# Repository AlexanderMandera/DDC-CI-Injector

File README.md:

# DDC/CI Injector using PCA9641

(work in progress, not working!)

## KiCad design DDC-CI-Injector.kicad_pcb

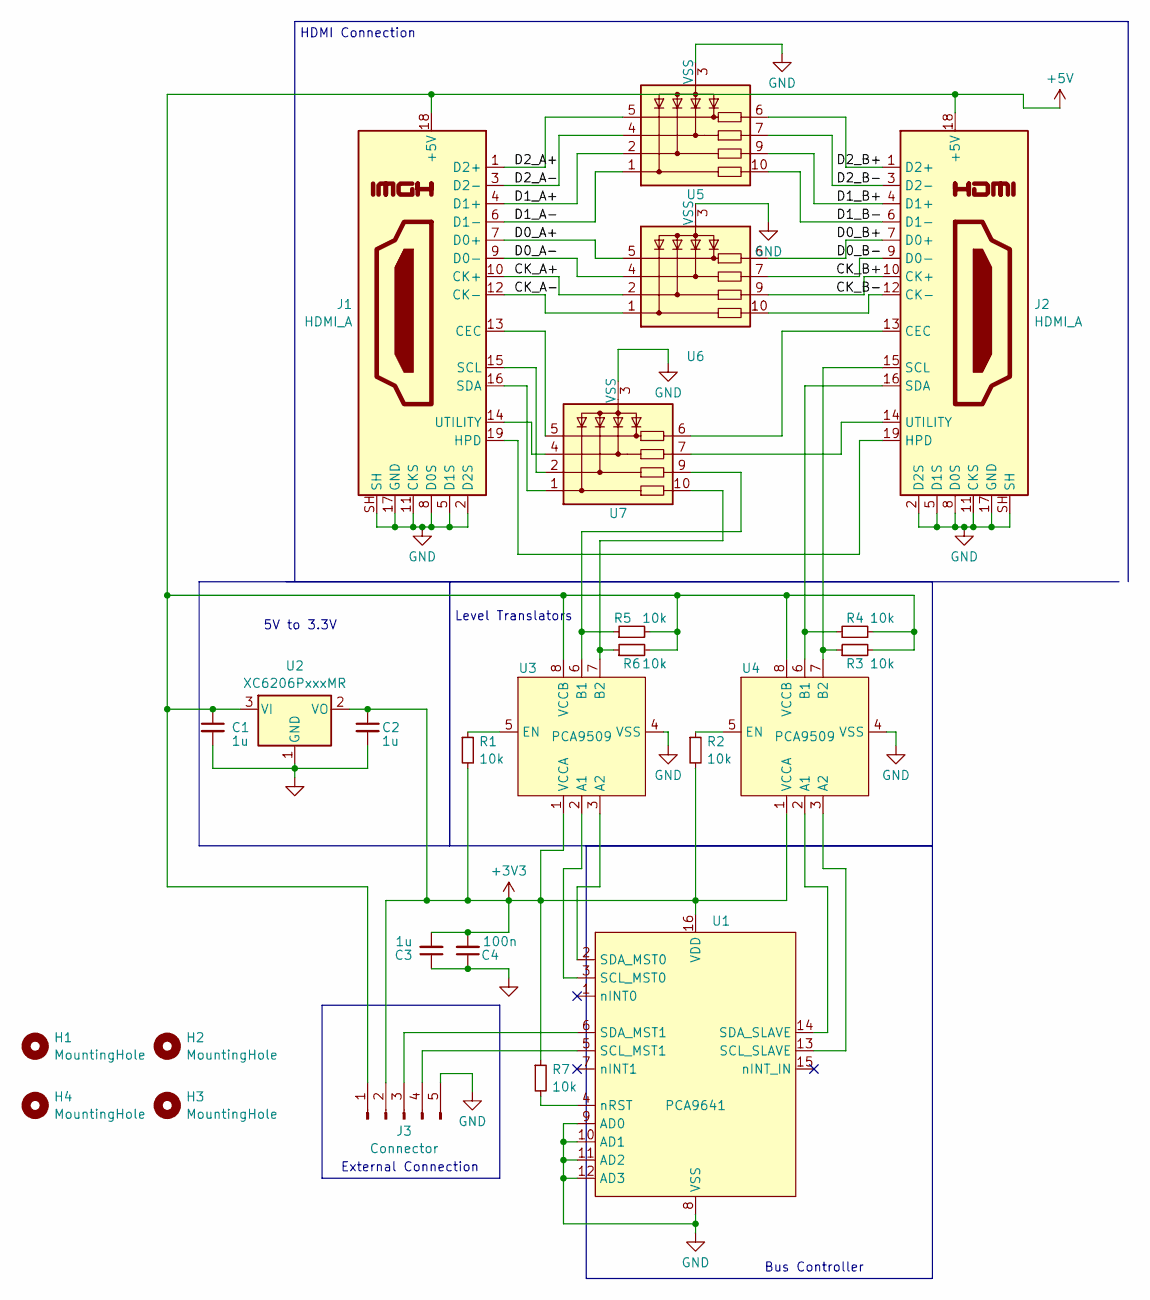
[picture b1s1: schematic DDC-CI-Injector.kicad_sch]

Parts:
C1, C2, C3: 1u; C_0603_1608Metric
C4: 100n; C_0402_1005Metric
H1, H2, H3, H4: MountingHole; MountingHole_2.7mm_M2.5_DIN965
J1, J2: HDMI_A; HDMI_A_Molex_208658-1001_Horizontal
J3: Connector; PinHeader_1x05_P2.54mm_Vertical
R1, R2, R3, R4, R5, R6, R7: 10k; R_0402_1005Metric
U1: PCA9641; TSSOP-16_4.4x5mm_P0.65mm
U2: XC6206PxxxMR; SOT-23-3
U3, U4: PCA9509; TSSOP-8_3x3mm_P0.65mm
U5, U6, U7: ESD224DQA; Diodes_UDFN-10_1.0x2.5mm_P0.5mm

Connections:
+3V3: C2.1, C3.2, C4.2, J3.2, R1.2, R2.2, R7.1, U1.16 (VDD), U2.2 (VO), U3.1 (VCCA), U4.1 (VCCA)
+5V: C1.1, J1.18 (+5V), J2.18 (+5V), J3.1, R3.2, R4.2, R5.2, R6.2, U2.3 (VI), U3.8 (VCCB), U4.8 (VCCB)
/CK_A+: J1.10 (CK+), U6.2
/CK_A-: J1.12 (CK-), U6.1
/CK_B+: J2.10 (CK+), U6.9
/CK_B-: J2.12 (CK-), U6.10
/D0_A+: J1.7 (D0+), U6.5
/D0_A-: J1.9 (D0-), U6.4
/D0_B+: J2.7 (D0+), U6.6
/D0_B-: J2.9 (D0-), U6.7
/D1_A+: J1.4 (D1+), U5.2
/D1_A-: J1.6 (D1-), U5.1
/D1_B+: J2.4 (D1+), U5.9
/D1_B-: J2.6 (D1-), U5.10
/D2_A+: J1.1 (D2+), U5.5
/D2_A-: J1.3 (D2-), U5.4
/D2_B+: J2.1 (D2+), U5.6
/D2_B-: J2.3 (D2-), U5.7
GND: C1.2, C2.2, C3.1, C4.1, J1.2 (D2S), J1.5 (D1S), J1.8 (D0S), J1.11 (CKS), J1.17 (GND), J1.SH, J2.2 (D2S), J2.5 (D1S), J2.8 (D0S), J2.11 (CKS), J2.17 (GND), J2.SH, J3.5, U1.8 (VSS), U1.9 (AD0), U1.10 (AD1), U1.11 (AD2), U1.12 (AD3), U2.1 (GND), U3.4 (VSS), U4.4 (VSS), U5.3 (VSS), U5.8 (VSS), U6.3 (VSS), U6.8 (VSS), U7.3 (VSS), U7.8 (VSS)
unnamed: J1.13 (CEC), U7.5
unnamed: J1.19 (HPD), J2.19 (HPD)
unnamed: J1.15 (SCL), U7.2
unnamed: J1.16 (SDA), U7.1
unnamed: J1.14 (UTILITY), U7.4
unnamed: J2.13 (CEC), U7.6
unnamed: J2.15 (SCL), R3.1, U4.7 (B2)
unnamed: J2.16 (SDA), R4.1, U4.6 (B1)
unnamed: J2.14 (UTILITY), U7.7
unnamed: J3.3, U1.6 (SDA_MST1)
unnamed: J3.4, U1.5 (SCL_MST1)
unnamed: U1.3 (SCL_MST0), U3.2 (A1)
unnamed: U1.13 (SCL_SLAVE), U4.3 (A2)
unnamed: U1.2 (SDA_MST0), U3.3 (A2)
unnamed: U1.14 (SDA_SLAVE), U4.2 (A1)
unnamed: R7.2, U1.4 (nRST)
unnamed: R5.1, U3.6 (B1), U7.9
unnamed: R6.1, U3.7 (B2), U7.10
unnamed: R1.1, U3.5 (EN)
unnamed: R2.1, U4.5 (EN)

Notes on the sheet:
HDMI Connection
Bus Controller
External Connection
Level Translators
5V to 3.3V

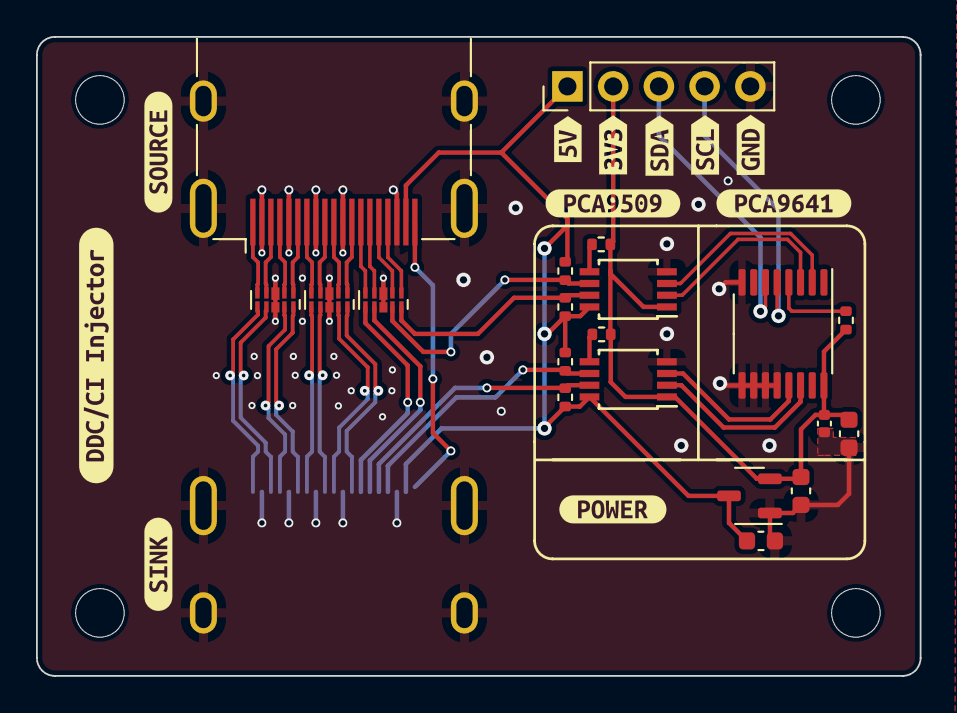
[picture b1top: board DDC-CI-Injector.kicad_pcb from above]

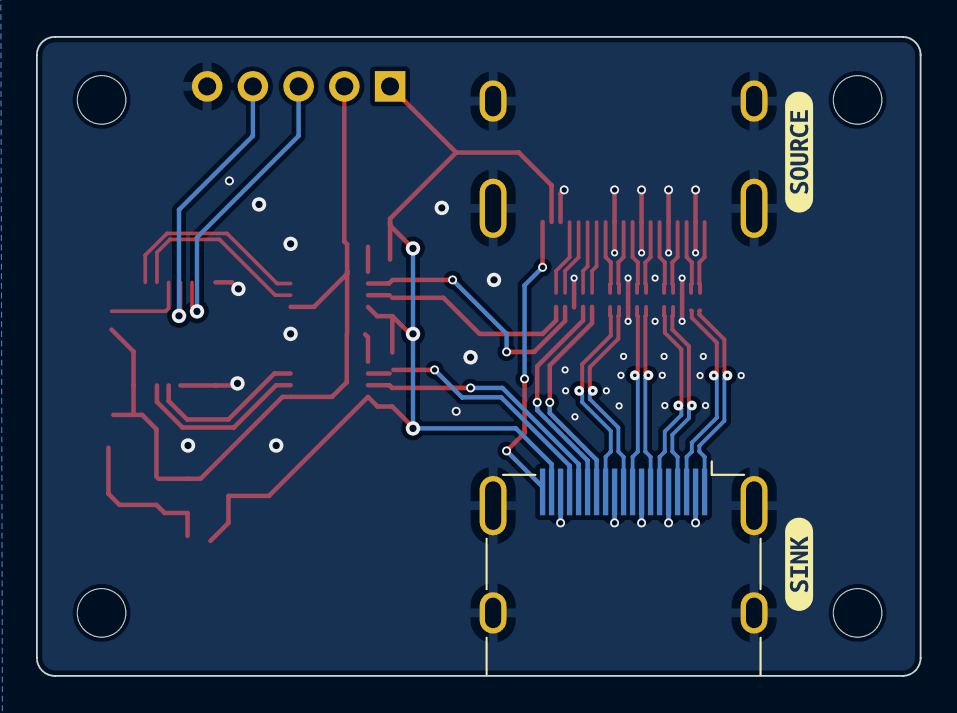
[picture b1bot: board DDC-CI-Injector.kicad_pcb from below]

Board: 4 copper layers, 49.1 x 35.5 mm, 38 parts (3 on the bottom side), 39 nets.

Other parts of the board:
kibuzzard-65C78A0C: G***; kibuzzard-65C78A0C
kibuzzard-65C78A2B: G***; kibuzzard-65C78A2B
kibuzzard-65C78A2F: G***; kibuzzard-65C78A2F
kibuzzard-65C78A34: G***; kibuzzard-65C78A34
kibuzzard-65C78A39: G***; kibuzzard-65C78A39
kibuzzard-65C78A58: G***; kibuzzard-65C78A58
kibuzzard-65C78CFB: G***; kibuzzard-65C78CFB
kibuzzard-65C788DA, kibuzzard-65C788DA#2: G***; kibuzzard-65C788DA
kibuzzard-65C788F4, kibuzzard-65C788F4#2: G***; kibuzzard-65C788F4
kibuzzard-65C7895D: G***; kibuzzard-65C7895D
kibuzzard-65C78967: G***; kibuzzard-65C78967

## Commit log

2024-02-06 Fix ground plane
2024-02-06 Better routing
2024-02-08 Fix small stuff
2024-02-11 Fix traces and other small stuff, add silkscreen
